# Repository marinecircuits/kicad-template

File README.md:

# Usage
- Create new project directory
  - `mkdir new-prorject && cd new-project`
- Copy content of repository
  - `curl -L https://github.com/marinecircuits/kicad-template/archive/refs/heads/main.tar.gz | tar -xz --strip-components=1`
- setup python environment `python3 -m venv .venv && source .venv/bin/activate && pip install -r requirements.txt`
- execute setup script
  - `python3 scripts/setup_template.py`
- init git repository (if not already done) and add all files `git init . && git add .`
- install pre-commit hook `pre-commit install --hook-type commit-msg`

# Variables
These variables are relevant for this template / workflow:
- `${ISSUE_DATE}`: the release PR workflow will update this with the current date, in the `YYYY-MM-DD` format (the only date format you should ever use by the way). It is committed and added in the PR as a change
- `${REVISION}`: the release PR will update this with the git tag (not 100% true, the git tag will be only created one the PR is merged into main, but the result is the same). It is committed and added in the PR as a change. This field will have `+!` appended if it's not a released version.
- `${COMMENT9}`: before kibot is invoked on github, this variable is updated with the short git hash from `git rev-parse --short HEAD`. It is committed and added in the PR as a change
- `${COMMENT8}`: This contains the project name. It is not updated automatically, you should set it once at the beginning of the project.

# Versioning
It follows the semantic versionin approach.
Schematics and PCB always have the same version.
Anything breaking functional interfaces will be a breaking change which increments the major version. 
This includes board shape, connector position.
TBD: will adding functionality without breaking interfaces just increment the minor version? Difficult to say if adding a connector will interfere with an existing case or other mechanical constraints.
Changes in schematics which do not affect anything electrical (documentation, re-organize wires) will increment a patch.
Changes in schematics which affect the value of a component, new connections, removal of components will increment a minor version.
# Assembly variant
This is a property of the BOM. At the moment variants are not fully supported (or better: only one variant is fully supported).
VARIANT.md lists all the different variants with a textual description with the differences with respect to variant 1.

# Github
In github you must allow actions to create pullrequest for this workflow to be working.
Under `Settings`, `Actions`, `General` this settings must be enabled. If greyed out, it must be enabled at the organization level.

# Description of usage
## Daily use
During daily work, the user branches off from main, makes changes, commits them, pushes to github, opens a PR, and merges the changes back to main. It is important to commit using the commitizen commit format, otherwise the whole versioning will not make sense. Checkout the [documentation](https://commitizen-tools.github.io/commitizen/tutorials/writing_commits/).
When a PR to main is opened, the jobs inside `.github/worflows/pullrequest.yml` get triggered.
The worflow will call `.github/workflows/module-kibot.yml`, which generates all the files needed for production.
In `kibot.yaml` the output files can be tweaked. The most important thing is to have `dont_stop` set to `false` under `preflight` in `erc` and `drc`, such that the workflow will fail and nothing broken is merged into main.
## Release process
### Pull request
A release is started by invoking the *Create Release PR* Action. This will trigger the jobs inside `.github/workflows/create-release-pr.yml`. 
First, commitizen will bump the version, create (update) the `CHANGELOG.md`.
Then the `date`, `rev`, `comment 9` fields are updated and committed to a release branch `release/v$VERSION`. Then, a pull request to main is opened.
The user can now inspect the changes and merge it.
### Release
Once the PR has been merged, the jobs inside `.github/workflows/tag-release-merge.yml` are triggered.
The job extracts the version from the pull request title and creates a corresponding tag on `main`. The kibot workflow is invoked, and artifacts are generated.
An official Github release `Release X.Y.Z` is created and the production files are uploaded to it.

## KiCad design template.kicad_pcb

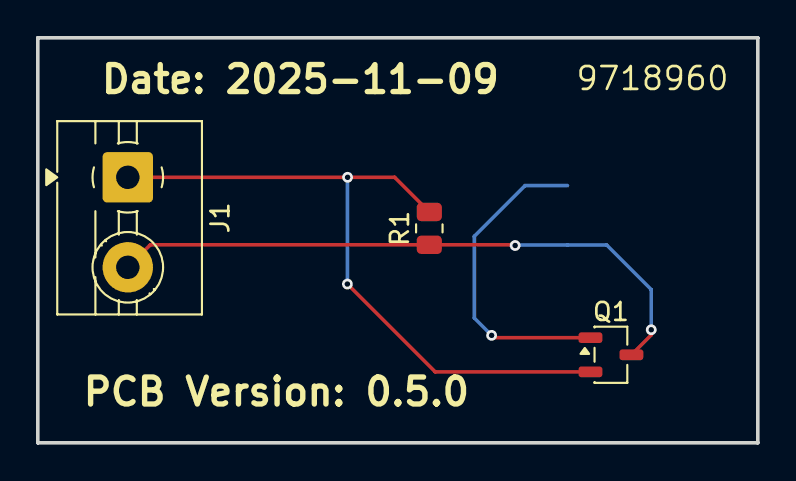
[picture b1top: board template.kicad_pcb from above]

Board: 2 copper layers, 40.0 x 22.5 mm, 4 parts (1 on the bottom side), 3 nets.

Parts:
D1: MBR0530; D_SOD-123
J1: Screw Terminal Block 5.00 mm 2 pol; TerminalBlock_MaiXu_MX126-5.0-02P_1x02_P5.00mm
Q1: BSS138; SOT-23-3
R1: 47k_0805; R_0805_2012Metric

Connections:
GND: J1.1, Q1.2 (S), R1.2
unnamed: D1.2 (A), J1.2, Q1.3 (D), R1.1
unnamed: D1.1 (K), Q1.1 (G)

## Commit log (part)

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2025-10-05 add first template
2025-10-05 fix: use placehodler for revision
2025-10-05 bump: version 0.0.1 → 0.0.2
2025-10-05 fix: udpate to semver2
2025-10-05 bump: version 0.0.2 → 0.0.3
2025-10-05 fix: add pre commit hook
2025-10-05 feat: add readme
2025-10-05 bump: version 0.0.3 → 0.1.0
2025-10-11 feat: add digikey order BOM
2025-10-11 feat: add dummy schematics + pcb
2025-10-11 fix: ignore ERC issue
2025-10-11 fix: build also on push to master
2025-10-11 ci: make ci scripts modular
2025-10-11 ci: update kibot script call conditions
2025-10-11 ci: add workflow to publish stable release
2025-10-11 ci: execute release script manually
2025-10-11 ci: push with force option
2025-10-11 ci: push using cz action
2025-10-11 ci: use dedicated push token
2025-10-11 bump: version 0.1.0 → 0.2.0
2025-10-11 feat: add version to PCB from latest tag
2025-10-11 feat: use only major version if released
2025-10-11 fix: execute version update also in release script
2025-10-11 feat: update version in schematics from git
2025-10-11 bump: version 0.2.0 → 0.3.0
2025-10-11 bump: version 0.3.0 → 0.4.0
2025-11-09 ci: add release workflow
2025-11-09 Revert "ci: add release workflow"
2025-11-09 ci: add forgotten files
2025-11-09 feat: add release workflow + add new text on PCB
2025-11-09 bump: version 0.4.0 → 0.5.0
2025-11-09 docs: update readme
2025-11-12 doc: update readme
2025-11-12 doc: fix url
2025-11-12 docs: add description of comment 8
2025-11-12 fix: don't make pipeline fail if there is no tag yet
2025-11-15 feat: add deployment script
2025-11-15 feat: ask while deployment interactively the project name
2025-11-15 doc: simplify python environment setup
2025-11-15 fix: use json cz file instad od toml
2025-11-15 fix: update json file for real now
2025-11-15 doc: add description how to init git repository
2025-11-15 fix: ignore .venv folder
2025-11-15 feat: add boostrap script for easy start
2025-11-16 fix: fix date update in sch/pcb files
2025-11-16 feat: remove 4x4 panel demo
2025-11-22 fix: reset the correct json version field
2025-12-09 doc: usage update
    Improve description of how to use template
2025-12-10 ci: rename release zip to repository name
2026-02-03 remove leading v from dummy tag
2026-02-04 ci: no need for change log in PR release branch
2026-02-04 ci: remove leading v from tag in output zip
2026-02-04 ci: don't generate 3d files by default
2026-02-07 fix: unify all BOMs in one directory
